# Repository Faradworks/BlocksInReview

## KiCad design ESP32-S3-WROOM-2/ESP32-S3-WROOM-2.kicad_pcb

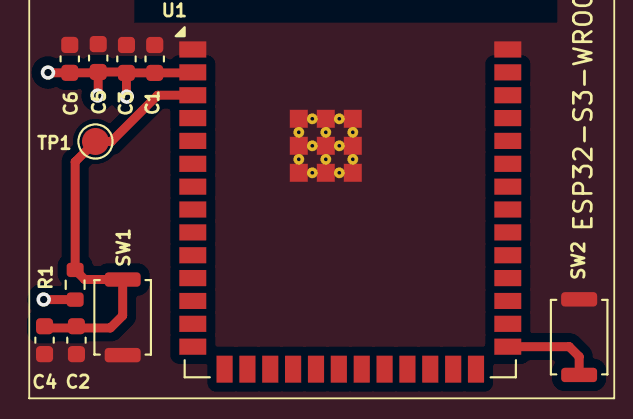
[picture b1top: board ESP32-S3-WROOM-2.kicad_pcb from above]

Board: 4 copper layers, 11 parts (0 on the bottom side), 4 nets.

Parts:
C1: 22uF; C_0603_1608Metric
C2: 1uF; C_0603_1608Metric
C3, C4, C5, C6: 0.1uF; C_0603_1608Metric
R1: 10k; R_0603_1608Metric
SW1, SW2: SW_Push; SW_Push_SPST_NO_Alps_SKRK
TP1: TestPoint; TestPoint_Pad_D1.5mm
U1: ESP32-S3-WROOM-2

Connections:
/block_ESP32-S3-WROOM-2/+3V3: C1.1, C3.1, C5.1, C6.1, R1.1, U1.2 (3V3)
/block_ESP32-S3-WROOM-2/GND: C1.2, C2.2, C3.2, C4.2, C5.2, C6.2, SW1.1, SW2.2, U1.1 (GND), U1.40 (GND), U1.41 (GND)
unnamed: C2.1, C4.1, R1.2, SW1.2, TP1.1, U1.3 (EN)
unnamed: SW2.1, U1.27 (IO0)

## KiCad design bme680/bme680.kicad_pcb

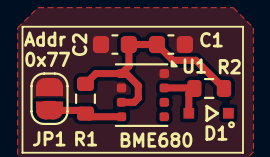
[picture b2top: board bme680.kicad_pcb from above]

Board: 4 copper layers, 7 parts (0 on the bottom side), 4 nets.

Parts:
C1: 10uF; C_0603_1608Metric
C2: 0.1uF; C_0603_1608Metric
D1: 1N4148WS; SOD323
JP1: Jumper_2_Open; SolderJumper-2_P1.3mm_Open_RoundedPad1.0x1.5mm
R1, R2: 10k; R_0603_1608Metric
U1: BME680; Bosch_LGA-8_3x3mm_P0.8mm_ClockwisePinNumbering

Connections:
/BME680/+3V3: C1.1, C2.1, R1.1, R2.1, U1.6 (VDDIO), U1.8 (VDD)
/BME680/GND: C1.2, C2.2, JP1.1 (A), U1.1 (GND), U1.7 (GND)
/BME680/SD0/ADDR: JP1.2 (B), R1.2, U1.5 (SDO)
unnamed: D1.A, R2.2, U1.2 (CSB)

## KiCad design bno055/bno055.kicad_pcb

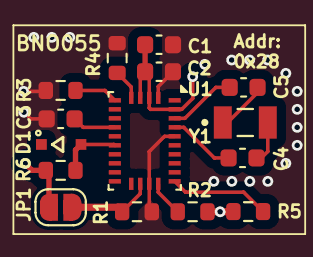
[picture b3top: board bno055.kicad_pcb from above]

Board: 4 copper layers, 15 parts (0 on the bottom side), 13 nets.

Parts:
C1: 10uF; C_0603_1608Metric
C2, C3: 0.1uF; C_0603_1608Metric
C4, C5: 22pF; C_0603_1608Metric
D1: 1N4148WS; SOD323
JP1: Jumper_2_Open; SolderJumper-2_P1.3mm_Open_RoundedPad1.0x1.5mm
R1, R2, R3, R4, R5, R6: 10k; R_0603_1608Metric
U1: BNO055; LGA-28_5.2x3.8mm_P0.5mm
Y1: NX3215SA-32.768K-STD-MUA-14; XTAL_NX3215SA-32.768K-STD-MUA-14

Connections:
/block_bno055/3V3: C1.1, C2.1, JP1.1 (A), R2.1, R5.1, R6.1, U1.3 (VDD), U1.4 (~BOOT_LOAD_PIN), U1.28 (VDDIO)
/block_bno055/GND: C1.2, C2.2, C3.2, R1.2, R3.2, R4.2, U1.2 (GND), U1.18 (COM2), U1.25 (GNDIO)
/block_bno055/SCL: R2.2, U1.19 (COM1)
/block_bno055/SDA: R5.2, U1.20 (COM0)
unnamed: C4.2, Y1.2
unnamed: C5.2, Y1.1
unnamed: JP1.2 (B), R1.1, U1.17 (COM3)
unnamed: C3.1, U1.9 (CAP)
unnamed: R3.1, U1.6 (PS0)
unnamed: R4.1, U1.5 (PS1)
unnamed: C5.1, U1.27 (XIN32)
unnamed: C4.1, U1.26 (XOUT32)
unnamed: D1.A, R6.2, U1.11 (~RESET)

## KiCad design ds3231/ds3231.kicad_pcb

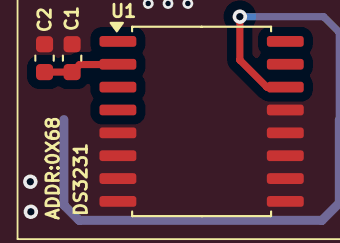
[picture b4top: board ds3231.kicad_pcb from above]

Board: 4 copper layers, 4 parts (1 on the bottom side), 3 nets.

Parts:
BT1: BAT-HLD-012-SMT; BAT_BAT-HLD-012-SMT
C1: 10uF; C_0603_1608Metric
C2: 0.1uF; C_0603_1608Metric
U1: DS3231M; SOIC-16W_7.5x10.3mm_P1.27mm

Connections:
/block_ds3231_rtc/GND: BT1.N, C1.2, C2.2, U1.5 (GND), U1.6 (GND), U1.7 (GND), U1.8 (GND), U1.9 (GND), U1.10 (GND), U1.11 (GND), U1.12 (GND), U1.13 (GND)
/block_ds3231_rtc/VCC: C1.1, C2.1, U1.2 (VCC)
unnamed: BT1.P1, BT1.P2, U1.14 (VBAT)

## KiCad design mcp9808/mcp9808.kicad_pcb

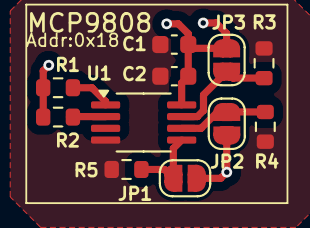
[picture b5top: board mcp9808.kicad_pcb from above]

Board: 4 copper layers, 11 parts (0 on the bottom side), 7 nets.

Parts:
C1: 10uF; C_0603_1608Metric
C2: 0.1uF; C_0603_1608Metric
JP1, JP2, JP3: Jumper_2_Open; SolderJumper-2_P1.3mm_Open_RoundedPad1.0x1.5mm
R1, R2, R3, R4, R5: 10k; R_0603_1608Metric
U1: MCP9808_MSOP; MSOP-8_3x3mm_P0.65mm

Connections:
/block_mcp9808/A0: JP3.1 (A), R3.1, U1.7 (A0)
/block_mcp9808/A1: JP2.1 (A), R4.1, U1.6 (A1)
/block_mcp9808/A2: JP1.1 (A), R5.1, U1.5 (A2)
/block_mcp9808/GND: C1.2, C2.2, R3.2, R4.2, R5.2, U1.4 (GND)
/block_mcp9808/VCC: C1.1, C2.1, JP1.2 (B), JP2.2 (B), JP3.2 (B), R1.1, R2.1, U1.8 (V_{DD})
unnamed: R2.2, U1.2 (SCL)
unnamed: R1.2, U1.1 (SDA)

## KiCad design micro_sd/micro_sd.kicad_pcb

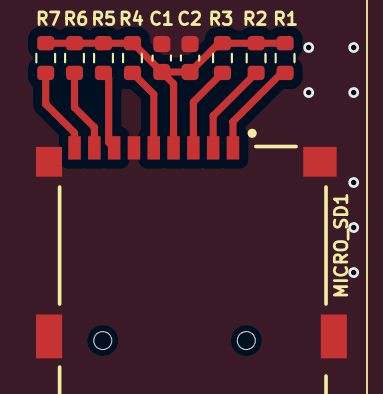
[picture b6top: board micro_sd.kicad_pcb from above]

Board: 4 copper layers, 10 parts (0 on the bottom side), 9 nets.

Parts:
C1: 10uF; C_0603_1608Metric
C2: 0.1uF; C_0603_1608Metric
MICRO_SD1: TF-01A
R1, R2, R3, R4, R5, R6, R7: 47K; R_0603_1608Metric

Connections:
/block_micro_sd/+3V3: C1.1, C2.1, MICRO_SD1.4 (VDD), R1.1, R2.1, R3.1, R4.1, R5.1, R6.1, R7.1
/block_micro_sd/CLK: MICRO_SD1.5 (CLK), R4.2
/block_micro_sd/CS: MICRO_SD1.2 (CD/DAT3), R2.2
/block_micro_sd/DAT1: MICRO_SD1.8 (DAT1), R6.2
/block_micro_sd/DAT2: MICRO_SD1.1 (DAT2), R1.2
/block_micro_sd/DET_A: MICRO_SD1.CD1 (CD), R7.2
/block_micro_sd/DI: MICRO_SD1.3 (CMD), R3.2
/block_micro_sd/DO: MICRO_SD1.7 (DAT0), R5.2
/block_micro_sd/GND: C1.2, C2.2, MICRO_SD1.6 (VSS), MICRO_SD1.MP1 (SHIELD), MICRO_SD1.MP2 (SHIELD), MICRO_SD1.MP3 (SHIELD), MICRO_SD1.MP4 (SHIELD)
